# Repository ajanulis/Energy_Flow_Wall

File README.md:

# Energy Flow Wall (Public)

Public hardware/reference repository for the Energy Flow Wall mesh-networked
ventilation valve system, organized by subsystem:

```
Actuator/   Window-frame-mounted valve unit — KiCad PCB designs, Fusion 360 case, manuals
Gateway/    Raspberry Pi + NC1000 mesh gateway — NeoCortec protocol docs
Device/     In-room e-paper touchscreen — hardware planning, procurement, datasheets, working-prototype photos
Docs/       Whole-system docs (functional requirements, architecture reference)
```

Source code (firmware, Gateway pipeline, Node-RED deploy scripts) is
maintained in a separate private repository.

---

## Actuator

The window-frame-mounted unit itself — PSoC5 + NC1000 mesh radio + motors + flaps + fan.

- [`Actuator/KiCad/`](Actuator/KiCad/) — PCB designs.
- [`Actuator/Actuator_EFW#4_based_on_8411A v4_non_symmetrical_case.f3d`](<Actuator/Actuator_EFW%234_based_on_8411A%20v4_non_symmetrical_case.f3d>) — Fusion 360 mechanical design (non-symmetrical case, v4). Open with Autodesk Fusion 360; all parametric history included. [Direct download](<https://github.com/ajanulis/Energy_Flow_Wall/raw/main/Actuator/Actuator_EFW%234_based_on_8411A%20v4_non_symmetrical_case.f3d>).
- [`Actuator/Manuals/DK_USER_MANUAL.md`](Actuator/Manuals/DK_USER_MANUAL.md) — End-user manual for the shipped demo unit: setup, dashboard usage, Demo Mode, troubleshooting.
- [`Actuator/Manuals/COMMANDS.md`](Actuator/Manuals/COMMANDS.md) — Developer/integrator reference: MQTT topics, JSON request format, full firmware command set, timeouts.

**Hardware**: PSoC 5 (CY8C5888LTQ-LP097) · DRV8411A motor driver · NC1000 mesh radio · UART 115200 baud.

## Gateway

Raspberry Pi 5 + NC1000 daughterboard, running NeoGateway + Node-RED +
the MQTT⇌mesh pipeline.

- [`Gateway/KiCad/Gateway_PCB/`](Gateway/KiCad/Gateway_PCB/) — the RPi/NC1000 HAT PCB design (moved here from `Actuator/KiCad/`, where it was previously grouped by mistake).
- [`Gateway/NeoCortec/`](Gateway/NeoCortec/) — NeoCortec integration manual, NC1000 datasheet, and UART communication spec — the protocol reference the Gateway pipeline implements against.

## Device

In-room e-paper touchscreen display. Custom PCB is still in the planning
stage, but a working touchscreen dashboard already runs end-to-end on an
STM32U5 Nucleo — see [`Device/README.md`](Device/README.md) for photos
and a walkthrough of what it does.

- [`Device/README.md`](Device/README.md) — working-prototype photos + what it does. **Start here.**
- [`Device/Brief.md`](Device/Brief.md) — architectural decisions + concept/scope.
- [`Device/Procurement.md`](Device/Procurement.md), [`Device/Datasheet_Stash.md`](Device/Datasheet_Stash.md) — parts sourcing and reference datasheets.
- [`Device/HW_Prep.md`](Device/HW_Prep.md), [`Device/Doc_Gaps.md`](Device/Doc_Gaps.md) — bring-up prep notes and known documentation gaps.

## Docs (whole-system)

- [`Docs/SYSTEM_REFERENCE.md`](Docs/SYSTEM_REFERENCE.md) — high-level system reference (architecture, mesh layout).
- [`Docs/EFW_Functional_Requirements_1.md`](Docs/EFW_Functional_Requirements_1.md) — original functional requirements document.

---

**Questions?** Contact the repository owner.

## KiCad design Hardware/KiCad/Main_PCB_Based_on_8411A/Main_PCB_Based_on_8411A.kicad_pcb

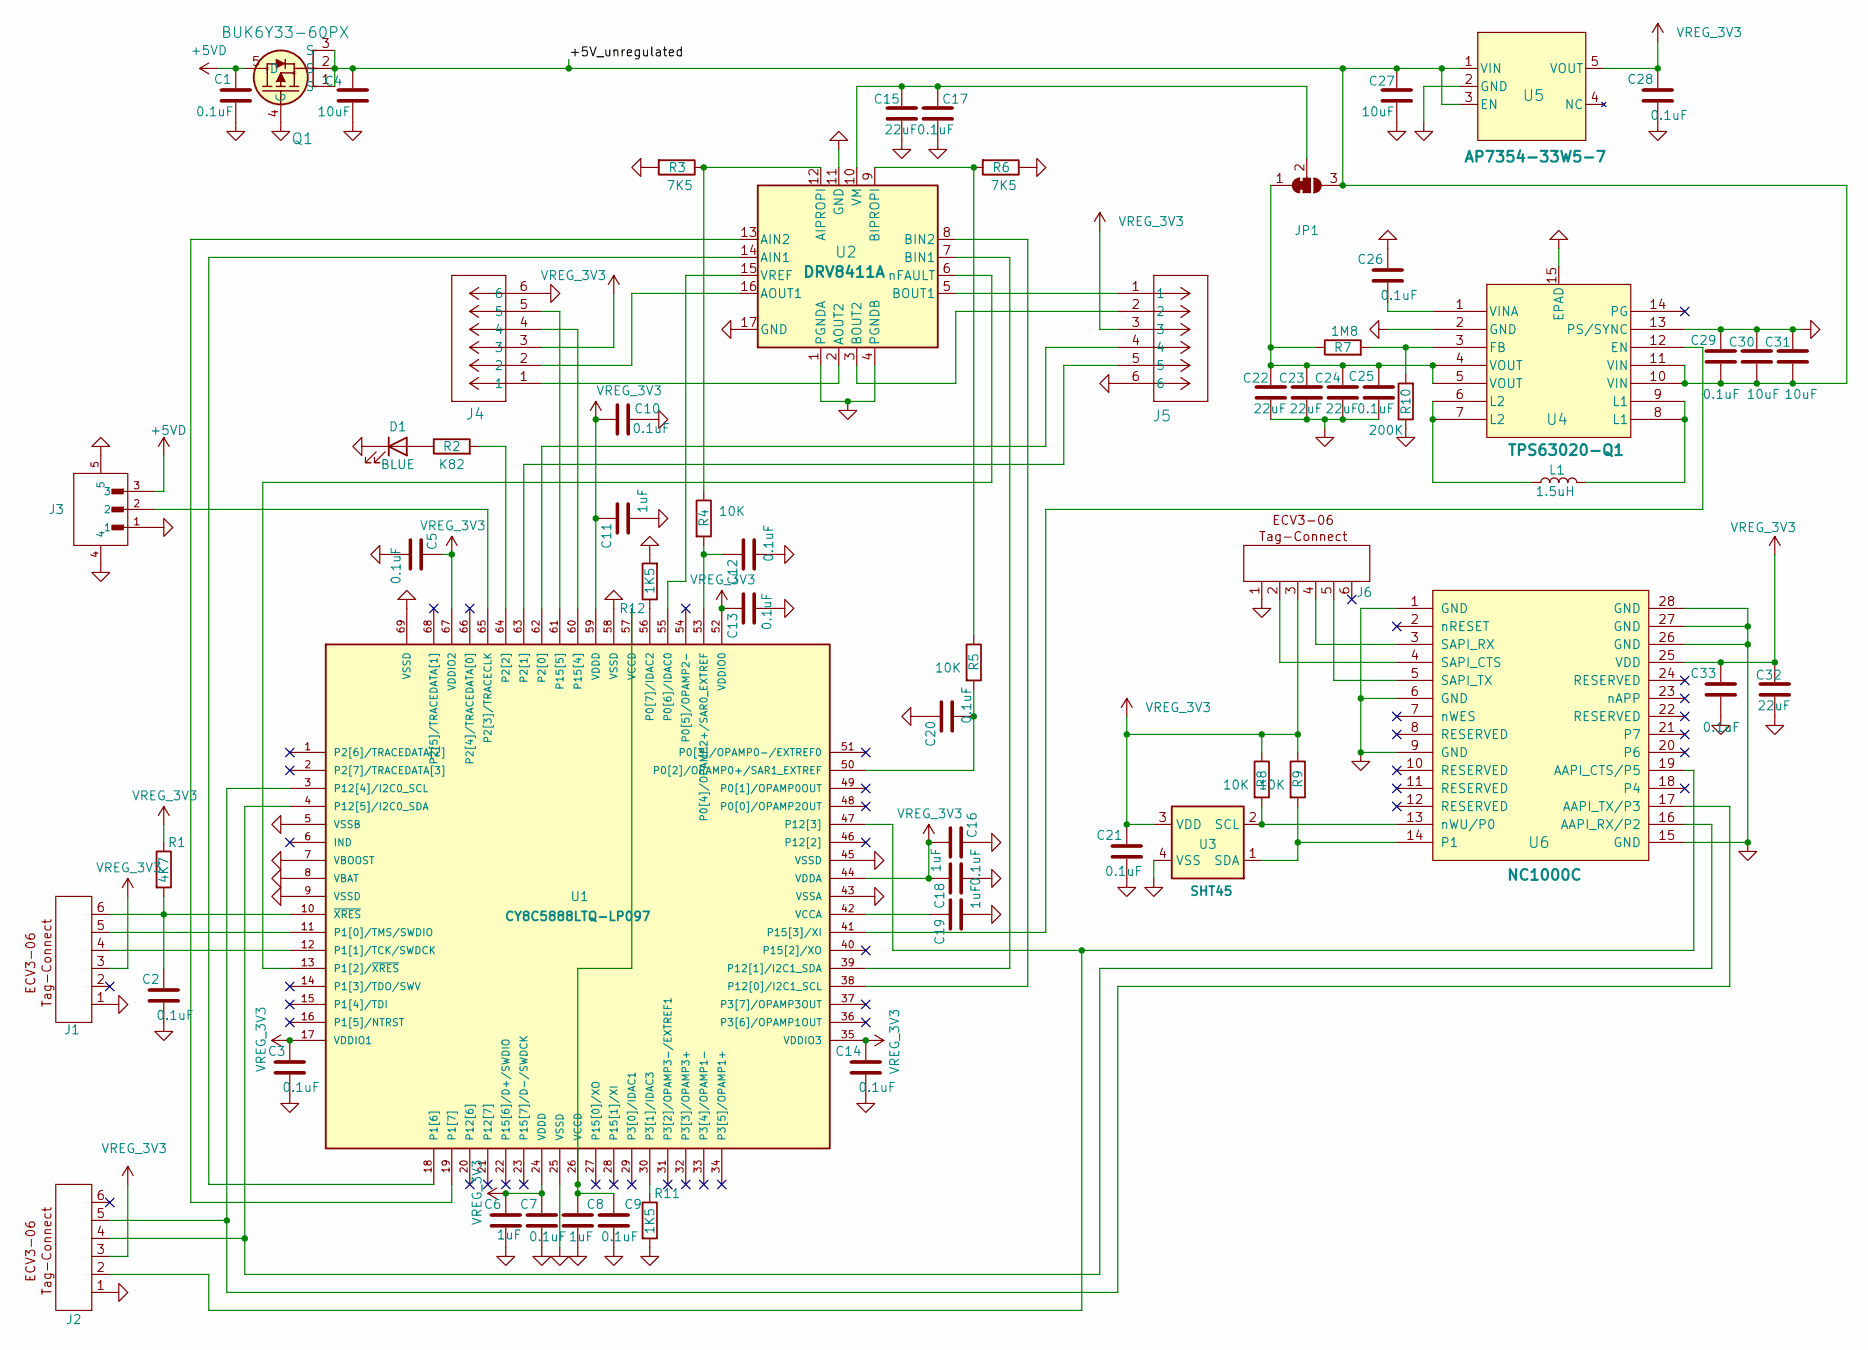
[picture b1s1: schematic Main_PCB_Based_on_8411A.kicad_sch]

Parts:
C1, C2, C3, C5, C7, C9, C10, C12, C13, C14, C17, C18, C20, C21, C25, C26, C28, C29, C33: 0.1uF; C_0402_1005Metric; MFR.Part # GRM155R71E104KE14D; JLCPCB Part # C77014
C4, C27, C30, C31: 10uF; C_0805_2012Metric; MFR.Part # GRM21BR71C106KE51L; JLCPCB Part # C408142
C6, C8, C11, C16, C19: 1uF; C_0402_1005Metric; MFR.Part # GRM155Z71A105KE01D; JLCPCB Part # C528974
C15, C22, C23, C24, C32: 22uF; C_0603_1608Metric; MFR.Part # GRM188R60J226MEA0D; JLCPCB Part # C77042
D1: BLUE; LED_0805_2012Metric; MFR.Part # LTST-C170TBKT; JLCPCB Part # C98222
J1, J2, J6: ECV3-06
J3: BM03B-PASS-1-TFT; JST_BM03B-PASS-1-TFT; PARTREV FEB.14.2024; JLCPCB Part # C485351
J4, J5: FM20C06VBNN
JP1: SolderJumper_3_Bridged12; SolderJumper-3_P1.3mm_Bridged12_RoundedPad1.0x1.5mm
L1: 1.5uH; L_Coilcraft_XxL4020; MFR.Part # XAL4020-152MEC; JLCPCB Part # C18547833
Q1: BUK6Y33-60PX; LFPAK_SOT669_NEX
R1: 4K7; R_0402_1005Metric; MFR.Part # AC0402FR-7W4K7L; JLCPCB Part # C5455562
R2: K82; R_0402_1005Metric; MFR.Part # 0402WGF8200TCE; JLCPCB Part # C25135
R3: 7K5; R_0402_1005Metric; MFR.Part # AC0402FR-7W7K5L; JLCPCB Part # C6117685
R4, R5, R8, R9: 10K; R_0402_1005Metric; MFR.Part # 0402WGF1002TCE; JLCPCB Part # C25744
R6: 7K5; R_0402_1005Metric; MFR.Part # AC0402FR-7W3K9L; JLCPCB Part # C6117679
R7: 1M8; R_0402_1005Metric; MFR.Part # RC0402FR-071M8L; JLCPCB Part # C185447
R10: 200K; R_0402_1005Metric; MFR.Part # 0402WGF2003TCE; JLCPCB Part # C25764
R11, R12: 1K5; R_0402_1005Metric; MFR.Part # AC0402FR-7W1K5L; JLCPCB Part # C5575287
U1: CY8C5888LTQ-LP097; QFN40P800X800X100-69N; PARTREV L
U2: DRV8411A; WQFN16_RTE_TEX; MFR.Part # DRV8411ARTER; JLCPCB Part # C18816315
U3: SHT45; SHT45_C_cutout_clean_new; MFR.Part # SHT45-AD1F-R2; JLCPCB Part # C5360602
U4: TPS63020-Q1; TPS63020QDSJRQ1; MFR.Part # TPS63020QDSJRQ1; JLCPCB Part # C2876554
U5: AP7354-33W5-7; SOT25_AP7354_DIO; MFR.Part # AP7354-33W5-7; JLCPCB Part # C460386
U6: NC1000C; NC1000c

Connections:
+5VD: C1.2, J3.3, Q1.5 (D)
/+5V_unregulated: C4.1, C27.1, C29.1, C30.2, C31.2, JP1.3 (B), Q1.1 (S), Q1.2 (S), Q1.3 (S), U4.10 (VIN), U4.11 (VIN), U5.1 (VIN), U5.3 (EN)
GND: C1.1, C2.1, C3.1, C4.2, C5.1, C6.1, C7.1, C8.1, C9.1, C10.1, C11.1, C12.1, C13.1, C14.1, C15.2, C16.2, C17.2, C18.1, C19.1, C20.2, C21.1, C22.2, C23.2, C24.2, C25.1, C26.2, C27.2, C28.1, C29.2, C30.1, C31.1, C32.2, C33.1, D1.1 (K), J1.1, J2.1, J3.1, J3.4, J3.5, J4.6, J5.6, J6.1, Q1.4 (G), R3.2, R6.1, R10.1, R11.2, R12.2, U1.5 (VSSB), U1.7 (VBOOST), U1.8 (VBAT), U1.9 (VSSD), U1.25 (VSSD), U1.43 (VSSA), U1.45 (VSSD), U1.58 (VSSD), U1.69 (VSSD), U2.1 (PGNDA), U2.4 (PGNDB), U2.11 (GND), U2.17 (GND), U3.4 (VSS), U4.2 (GND), U4.13 (PS/SYNC), U4.15 (EPAD), U5.2 (GND), U6.1 (GND), U6.6 (GND), U6.9 (GND), U6.15 (GND), U6.26 (GND), U6.27 (GND), U6.28 (GND)
unnamed: C8.2, C9.2, U1.26 (VCCD), U1.57 (VCCD)
unnamed: D1.2 (A), R2.1
unnamed: C22.1, C23.1, C24.1, C25.2, JP1.1 (A), R7.1, U4.4 (VOUT), U4.5 (VOUT)
unnamed: C15.1, C17.1, JP1.2 (C), U2.10 (VM)
unnamed: L1.1, U4.6 (L2), U4.7 (L2)
unnamed: L1.2, U4.8 (L1), U4.9 (L1)
unnamed: C20.1, R5.2, U1.50 (P0[2]/OPAMP0+/SAR1_EXTREF)
unnamed: C12.2, R4.2, U1.53 (P0[4]/OPAMP2+/SAR0_EXTREF)
unnamed: U1.55 (P0[6]/IDAC0), U2.15 (VREF)
unnamed: R12.1, U1.56 (P0[7]/IDAC2)
unnamed: J1.5, U1.11 (P1[0]/TMS/SWDIO)
unnamed: J1.4, U1.12 (P1[1]/TCK/SWDCK)
unnamed: U1.13 (P1[2]/~XRES), U2.6 (nFAULT)
unnamed: U1.18 (P1[6]), U2.14 (AIN1)
unnamed: U1.19 (P1[7]), U2.13 (AIN2)
unnamed: J5.4, U1.62 (P2[0])
unnamed: J5.5, U1.63 (P2[1])
unnamed: R2.2, U1.64 (P2[2])
unnamed: J3.2, U1.65 (P2[3]/TRACECLK)
unnamed: R11.1, U1.30 (P3[1]/IDAC3)
unnamed: U1.38 (P12[0]/I2C1_SCL), U2.8 (BIN2)
unnamed: U1.39 (P12[1]/I2C1_SDA), U2.7 (BIN1)
unnamed: J2.2, U1.47 (P12[3]), U6.19 (AAPI_CTS/P5)
unnamed: J2.5, U1.3 (P12[4]/I2C0_SCL), U6.17 (AAPI_TX/P3)
unnamed: J2.4, U1.4 (P12[5]/I2C0_SDA), U6.16 (AAPI_RX/P2)
unnamed: U1.41 (P15[3]/XI), U4.12 (EN)
unnamed: J4.4, U1.60 (P15[4])
unnamed: J4.5, U1.61 (P15[5])
unnamed: C19.2, U1.42 (VCCA)
unnamed: C2.2, J1.6, R1.2, U1.10 (~XRES)
unnamed: R3.1, R4.1, U2.12 (AIPROPI)
unnamed: J4.2, U2.16 (AOUT1)
unnamed: J4.1, U2.2 (AOUT2)
unnamed: R5.1, R6.2, U2.9 (BIPROPI)
unnamed: J5.1, U2.5 (BOUT1)
unnamed: J5.2, U2.3 (BOUT2)
unnamed: R8.2, U3.2 (SCL), U6.13 (nWU/P0)
unnamed: R9.2, U3.1 (SDA), U6.14 (P1)
unnamed: R7.2, R10.2, U4.3 (FB)
unnamed: C26.1, U4.1 (VINA)
unnamed: J6.2, U6.4 (SAPI_CTS)
unnamed: J6.4, U6.3 (SAPI_RX)
unnamed: J6.5, U6.5 (SAPI_TX)
VREG_3V3: C3.2, C5.2, C6.2, C7.2, C10.2, C11.2, C13.2, C14.2, C16.1, C18.2, C21.2, C28.2, C32.1, C33.2, J1.3, J2.3, J4.3, J5.3, J6.3, R1.1, R8.1, R9.1, U1.17 (VDDIO1), U1.24 (VDDD), U1.35 (VDDIO3), U1.44 (VDDA), U1.52 (VDDIO0), U1.59 (VDDD), U1.67 (VDDIO2), U3.3 (VDD), U5.5 (VOUT), U6.25 (VDD)

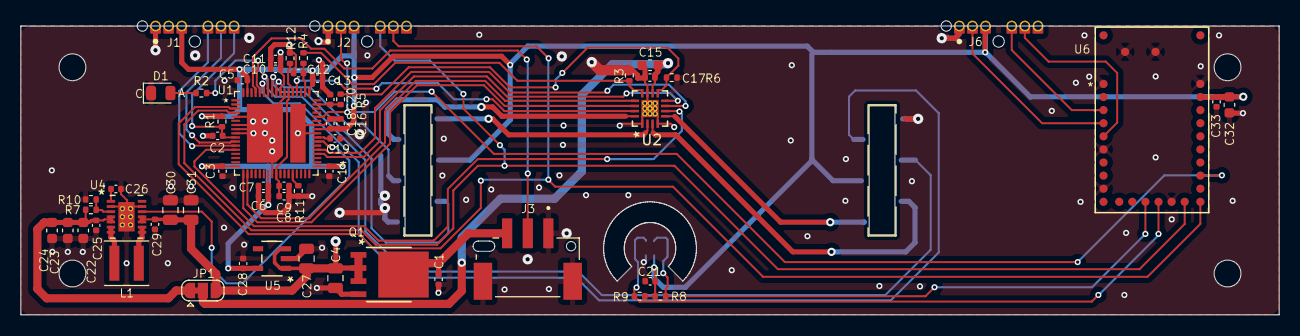
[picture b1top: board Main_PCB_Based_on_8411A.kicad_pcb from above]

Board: 2 copper layers, 122.0 x 28.0 mm, 61 parts (1 on the bottom side), 47 nets.

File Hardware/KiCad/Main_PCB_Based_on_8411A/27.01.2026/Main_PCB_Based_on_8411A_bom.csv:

Comment,Designator,Footprint,JLCPCB Part #,MFR.Part #,Qty,DNP,Exclude from BOM,Exclude from Board,Datasheet
0.1uF,"C1,C2,C3,C5,C7,C9,C10,C12,C13,C14,C17,C18,C20,C21,C25,C26,C28,C29,C33",Capacitor_SMD:C_0402_1005Metric,C77014,GRM155R71E104KE14D,19,,,,~
10uF 16V,"C4,C27",Capacitor_SMD:C_0805_2012Metric,C408142,GRM21BR71C106KE51L,2,,,,~
1uF,"C6,C8,C11,C16,C19",Capacitor_SMD:C_0402_1005Metric,C528974,GRM155Z71A105KE01D,5,,,,~
22uF,"C15,C22,C23,C24,C32",Capacitor_SMD:C_0603_1608Metric,C77042,GRM188R60J226MEA0D,5,,,,~
10uF,"C30,C31",Capacitor_SMD:C_0805_2012Metric,C408142,GRM21BR71C106KE51L,2,,,,~
BLUE,D1,LED_SMD:LED_0805_2012Metric,C98222,LTST-C170TBKT,1,,,,~
ECV3-06,"J1,J2,J6",Tag-Connect-ECV3-Footprints:ECV3-06,,,3,,Excluded from BOM,,
BM03B-PASS-1-TFT,J3,BM03B_PASS_1_TFT:JST_BM03B-PASS-1-TFT,C485351,BM03B-PASS-1-TFT(LF)(SN),1,,,,
FM20C06VBNN,"J4,J5",FM20C06VBNN:FM20C06VBNN,,,2,,,,FM20C06VBNN
SolderJumper_3_Bridged12,JP1,Jumper:SolderJumper-3_P1.3mm_Bridged12_RoundedPad1.0x1.5mm,,,1,,Excluded from BOM,,~
1.5uH,L1,Inductor_SMD:L_Coilcraft_XxL4020,C18547833,XAL4020-152MEC,1,,,,~
BUK6Y33-60PX,Q1,BUK6Y33-60P:LFPAK_SOT669_NEX,,,1,,,,BUK6Y33-60PX
4K7,R1,Resistor_SMD:R_0402_1005Metric,C5455562,AC0402FR-7W4K7L,1,,,,~
K82,R2,Resistor_SMD:R_0402_1005Metric,C25135,0402WGF8200TCE,1,,,,~
7K5,R3,Resistor_SMD:R_0402_1005Metric,C6117685,AC0402FR-7W7K5L,1,,,,~
10K,"R4,R5,R8,R9",Resistor_SMD:R_0402_1005Metric,C25744,0402WGF1002TCE,4,,,,~
7K5,R6,Resistor_SMD:R_0402_1005Metric,C6117679,AC0402FR-7W3K9L,1,,,,~
1M8,R7,Resistor_SMD:R_0402_1005Metric,C185447,RC0402FR-071M8L,1,,,,~
200K,R10,Resistor_SMD:R_0402_1005Metric,C25764,0402WGF2003TCE,1,,,,~
1K5,"R11,R12",Resistor_SMD:R_0402_1005Metric,C5575287,AC0402FR-7W1K5L,2,,,,~
CY8C5888LTQ-LP097,U1,CY8C5888LTQ-LP097:QFN40P800X800X100-69N,,,1,,,,
DRV8411A,U2,DRV8411ARTER:WQFN16_RTE_TEX,C18816315,DRV8411ARTER,1,,,,https://www.ti.com/lit/gpn/drv8411a
SHT45,U3,SHT45-AD1F-R2:SHT45_C_cutout_clean_new,C5360602,SHT45-AD1F-R2,1,,,,https://sensirion.com/media/documents/33FD6951/624C4357/Data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
TPS63020-Q1,U4,TPS63020QDSJRQ1:TPS63020QDSJRQ1,C2876554,TPS63020QDSJRQ1,1,,,,https://www.ti.com/lit/gpn/tps63020-q1
AP7354-33W5-7,U5,AP7354:SOT25_AP7354_DIO,C460386,AP7354-33W5-7,1,,,,AP7354-33W5-7
NC1000C,U6,NeoCortec:NC1000c,,,1,,,,

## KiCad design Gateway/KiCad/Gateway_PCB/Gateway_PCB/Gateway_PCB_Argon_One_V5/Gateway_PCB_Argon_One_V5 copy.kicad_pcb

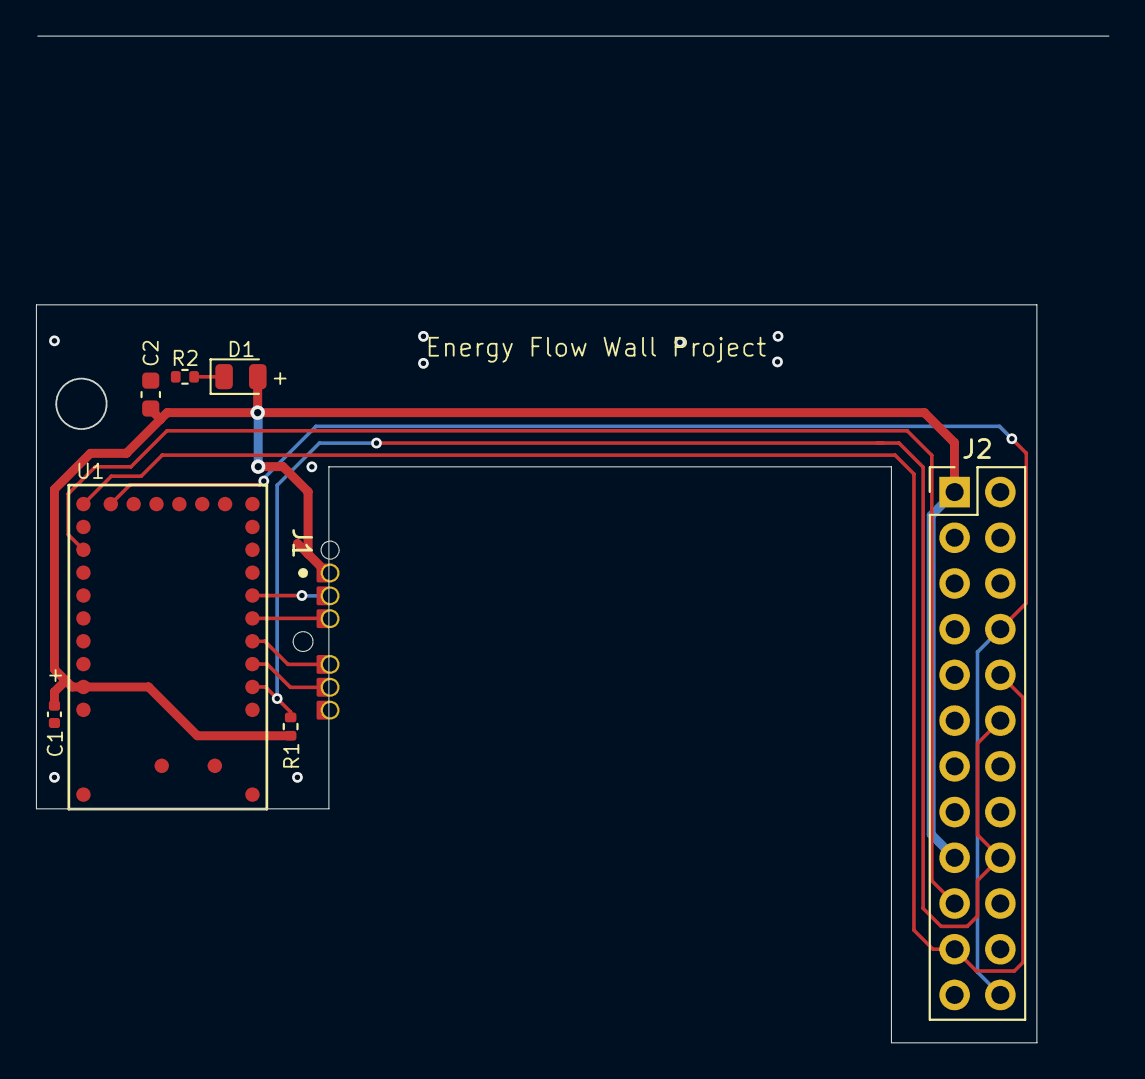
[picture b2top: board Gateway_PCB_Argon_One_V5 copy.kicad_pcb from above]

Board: 2 copper layers, 55.6 x 41.0 mm, 8 parts (0 on the bottom side), 7 nets.

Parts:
C1: 0.1uF; C_0402_1005Metric
C2: 22uF; C_0603_1608Metric
D1: BLUE; LED_0805_2012Metric
J1: Conn_01x06_Pin; ECV3-06
J2: Conn_02x12_Odd_Even; PinHeader_2x12_P2.54mm_Vertical
R1: 10K; R_0402_1005Metric
R2: K82; R_0402_1005Metric
U1: NC1000

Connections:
+3V3: C1.1, C2.1, D1.2 (A), J1.1, J2.1, J2.17, R1.1, U1.25 (VDD)
GND: C1.2, C2.2, J1.2, J2.6, J2.9, J2.14, J2.20, R2.2, U1.1 (GND), U1.6 (GND), U1.9 (GND), U1.15 (GND), U1.26 (GND), U1.27 (GND), U1.28 (GND)
unnamed: D1.1 (K), R2.1
unnamed: J2.10, J2.21, U1.17 (AAPI_TX/P3)
unnamed: J2.11, J2.19, U1.19 (AAPI_CTS/P5)
unnamed: J2.12, J2.18, R1.2, U1.2 (nRESET)
unnamed: J2.8, J2.24, U1.16 (AAPI_RX/P2)

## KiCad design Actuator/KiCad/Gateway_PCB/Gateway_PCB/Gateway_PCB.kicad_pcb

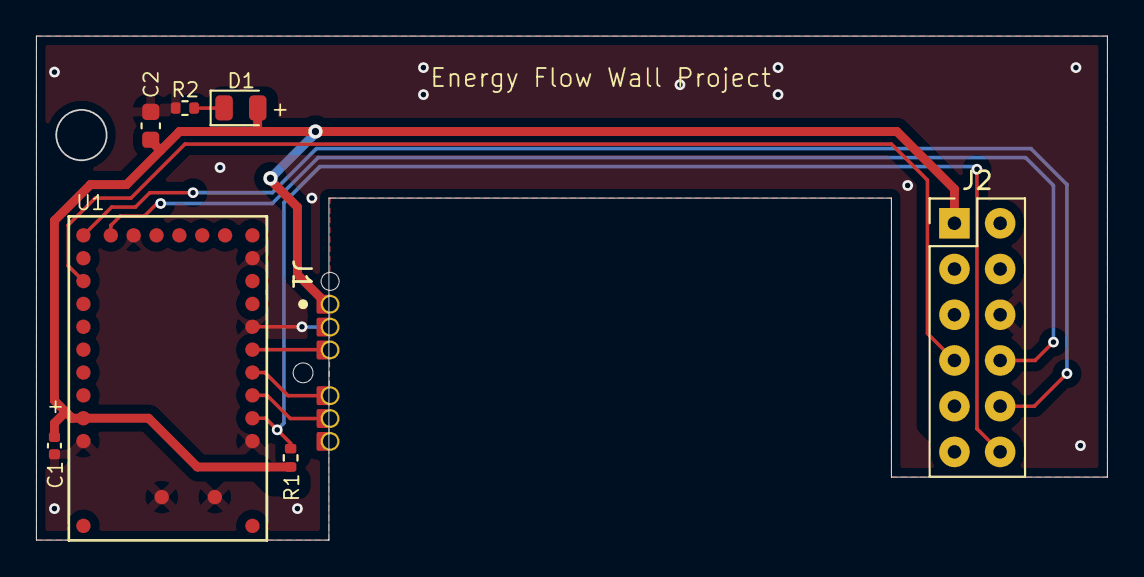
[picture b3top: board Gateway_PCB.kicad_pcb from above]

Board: 2 copper layers, 59.5 x 28.0 mm, 8 parts (0 on the bottom side), 7 nets.

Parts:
C1: 0.1uF; C_0402_1005Metric
C2: 22uF; C_0603_1608Metric
D1: BLUE; LED_0805_2012Metric
J1: Conn_01x06_Pin; ECV3-06
J2: Conn_02x06_Odd_Even; PinHeader_2x06_P2.54mm_Vertical
R1: 10K; R_0402_1005Metric
R2: K82; R_0402_1005Metric
U1: NC1000

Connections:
+3V3: C1.1, C2.1, D1.2 (A), J1.1, J2.1, R1.2, U1.25 (VDD)
GND: C1.2, C2.2, J1.2, J2.6, J2.9, R2.2, U1.1 (GND), U1.6 (GND), U1.9 (GND), U1.15 (GND), U1.26 (GND), U1.27 (GND), U1.28 (GND)
unnamed: D1.1 (K), R2.1
unnamed: J2.7, U1.19 (AAPI_CTS/P5)
unnamed: J2.8, U1.16 (AAPI_RX/P2)
unnamed: J2.10, U1.17 (AAPI_TX/P3)
unnamed: J2.12, R1.1, U1.2 (nRESET)

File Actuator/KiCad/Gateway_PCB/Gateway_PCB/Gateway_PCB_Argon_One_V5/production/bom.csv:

Designator,Footprint,Quantity,Value,LCSC Part #
C1,0402,1,0.1uF,C77014
C2,0603,1,22uF,C77042
D1,0805,1,BLUE,C98222
J2,PinHeader_2x12_P2.54mm_Vertical,1,Conn_02x12_Odd_Even,
R1,0402,1,10K,C25744
R2,0402,1,K82,C25135
U1,NC1000,1,NC1000,

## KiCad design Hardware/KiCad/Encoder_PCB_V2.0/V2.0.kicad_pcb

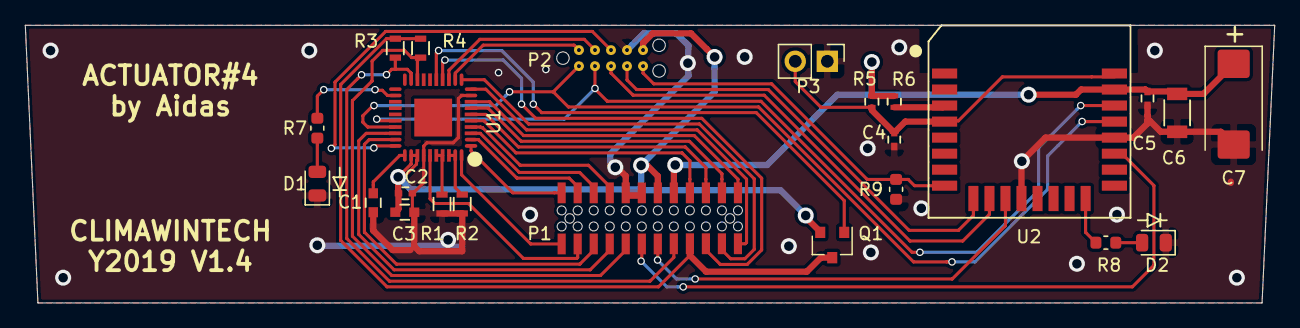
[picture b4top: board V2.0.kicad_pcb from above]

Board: 2 copper layers, 99.0 x 22.0 mm, 24 parts (0 on the bottom side), 41 nets.

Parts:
C1, C3: 1uF; C_0603
C2, C4, C5: 0.1uF; C_0402
C6: 10uF; C_1206
C7: 470uF; CP_EIA-7343-31_Kemet-D_Pad2.25x2.55mm_HandSolder
D1, D2: LED; LED_0805_2012Metric
P1: CONN_02X12; Pin_Header_Straight_2x12_Pitch1.27mm_w_holes
P2: TC2050-IDC; TC2050-IDC_NL
P3: CONN_01X02; PinHeader_1x02_P2.54mm_Vertical
Q1: IRLML6402; SOT-23
R1, R2: 1K5; R_0603
R3, R4: 4K7; R_0603
R5, R6: 100K; R_0402
R7, R8: 220; R_0603_1608Metric
R9: 10K; R_0603_1608Metric
U1: CY8C4245LQI-483; QFN40-6x6
U2: PSF-B85

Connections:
+3.3VP: C5.1, C6.1, C7.1, P1.15, R5.1, R6.1, U2.23
+3V3: C2.1, C3.1, P1.13, P2.6, Q1.2, U1.32, U1.33
GNDREF: C1.2, C2.2, C3.2, C4.2, C5.2, C6.2, C7.2, D1.1, D2.1, P1.9, P1.11, P2.7, P3.1, R1.2, R2.2, R9.1, U1.9, U1.34, U2.12, U2.20
unnamed: C1.1, U1.31
unnamed: C4.1, P3.2, R5.2, U2.4, U2.24
unnamed: D1.2, R7.2
unnamed: D2.2, R8.2
unnamed: P1.1, U1.1
unnamed: P1.2, U1.40
unnamed: P1.3, U1.2
unnamed: P1.4, U1.35
unnamed: P1.5, U1.3
unnamed: P1.6, U1.29
unnamed: P1.7, U1.4
unnamed: P1.8, U1.28
unnamed: P1.10, R4.2, U1.18
unnamed: P1.12, U2.19
unnamed: P1.14, U2.11
unnamed: P1.16, R3.2, U1.19
unnamed: P1.17, U1.5
unnamed: P1.18, Q1.3, R3.1, R4.1
unnamed: P1.19, U1.6
unnamed: P1.20, U1.14
unnamed: P1.21, U1.7
unnamed: P1.22, U1.11
unnamed: P1.23, U1.8
unnamed: P1.24, U1.10
unnamed: P2.1, U1.27, U2.21
unnamed: P2.2, U1.26, U2.22
unnamed: P2.3, U2.10
unnamed: P2.4, U2.9
unnamed: P2.5, R9.2, U2.8
unnamed: P2.8, U1.30
unnamed: P2.9, U1.13
unnamed: P2.10, U1.12
unnamed: Q1.1, U1.15
unnamed: R1.1, U1.36, U1.37
unnamed: R2.1, U1.38, U1.39
unnamed: R6.2, U2.3
unnamed: R7.1, U1.22
unnamed: R8.1, U2.16

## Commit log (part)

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2026-01-15 Update README for public CAD sharing only
